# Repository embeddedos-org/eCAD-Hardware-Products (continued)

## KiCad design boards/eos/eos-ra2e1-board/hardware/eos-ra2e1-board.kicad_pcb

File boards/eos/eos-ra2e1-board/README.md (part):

# EoS RA2E1 Board

A Renesas RA2E1 (R7FA2E1A92DFM, Cortex-M23, LQFP-64) development board that fits Arduino Uno R3 shields and Digilent Pmod modules, 68.58 × 53.34 mm, two layers.
Designed by Kartikeydheer Srivastava. All rights reserved: not open source, and not under this repository's MIT licence.
Anyone may view it, clone this repository and run its tests; anything more needs
Kartikeydheer Srivastava's written permission (kartikeydheer@gmail.com). EmbeddedOS (EoS) Research Foundation has a limited, revocable
permission. See [LICENSE.txt](LICENSE.txt) and [the licence summary](../README.md#licence).

A board for the same job as Renesas' EK-RA2E1; an original design, not a copy: no file of the vendor's was used.
No design file of the vendor's was used (no schematic, layout, CAD, Gerbers or BOM of Renesas' was opened);
the header positions come from Matthew Beckler's "Arduino Uno R3" dimension drawing v1.05, the Arduino UNO R3 product reference manual (A000066),
section 5.4, and Digilent's Pmod Interface Specification (revised 29 September 2020), section 4 and Figure 5.
The circuit comes from Renesas' RA2E1 data sheet, hardware manual and application notes, and the other
chip makers' data sheets.

| | |
|---|---|
|  |  |

The RA2E1 runs at 3.3 V from its 48 MHz on-chip oscillator. One USB-C port powers the board and
carries a CP2102N USB-UART bridge on SCI9, the RA2E1's serial-programming port, so the same port is
the console and, with the MD jumper fitted, the flash programmer. An Arm 10-pin SWD header takes
any SWD probe. The I/O runs at 3.3 V: IOREF is 3.3 V, and most RA2E1 pins take at most VCC + 0.3 V.

## What is on it

Sources: **DS** = Renesas RA2E1 Group Datasheet R01DS0386EJ0170 Rev.1.70; **UM** = RA2E1 Group
User's Manual: Hardware R01UH0852EJ0170 Rev.1.70; **QDG** = RA2 Quick Design Guide R01AN6060EU0104
Rev.1.04; **E2** = E2/E2 Lite Notes on Connection of RA Devices R20UT4686EJ0360 Rev.3.60; **CLK** =
Design Guide for Main Clock Circuits and Sub Clock Circuits R01AN7202EJ0102 Rev.1.02.

| Block | What it is, and where each value comes from |
|---|---|
| MCU | R7FA2E1A92DFM, 128 KB flash, 16 KB SRAM, −40 to 85 °C, LQFP-64 10 × 10 mm, 0.5 mm pitch (DS Table 1.12). KiCad's stock LQFP-64_10x10mm_P0.5mm footprint, checked against both package drawings the DS gives this part (Appendix 2, Figures A2.1 PLQP0064KB-C and A2.2 PLQP0064KL-A: body 10.0 mm, lead span 12.0 mm, leads 0.15–0.27 mm wide, foot 0.45–0.75 mm). |
| Supplies | 0.1 µF at each VCC/VSS pair (11/8, 39/40) (DS 2.1); 4.7 µF ceramic on VCL, the internal regulator's output (UM Table 38.1). AVCC0 must equal VCC and rise with or after it (DS Table 2.2): it comes from 3.3 V through a Bourns MH1608-221Y bead, with 0.1 µF at the pin and 10 µF + 10 nF at the supply (UM Figure 29.33, reference values). VREFH0 is tied to AVCC0 and VREFL0 to AVSS0, with 0.1 µF between them (DS 2.1, Table 1.14; UM Table 17.4). |
| 3.3 V LDO | TI TPS7A91 (SBVS282A), 1 A, from the 5 V rail: R1 = 3.57 kΩ, R2 = 1.15 kΩ (3.283 V, Table 7-1, Panasonic ERA-2AEB 0.1 %), 10 µF in (16 V 0805, so the 5 V bias costs less of it than the 50 % that section 7.1.3 allows for) and out, EN tied to IN. The RA2E1 needs its supply to rise at 0.02–2 ms/V (DS Table 2.14; 2 ms/V the limit in SCI boot mode). The TPS7A91's ramp has limits: tSS = 0.8 V × CNR/SS / INR/SS (Equation 6), INR/SS = 4.0–9.0 µA (section 5.5), so 10 nF ±10 % gives 0.80–2.2 ms, 0.24–0.67 ms/V. A plain LDO gives only a typical start-up time. That sum assumes the 5 V rail itself rises faster than about 0.5 V/ms: with EN tied to IN, a slower 5 V (a bench supply on the shield's 5V pin) is followed by the output and can break the 2 ms/V limit. Firmware that sets OFS1.LVDAS = 0 (voltage monitor 0 reset on at start-up) removes the upper limit outside SCI boot mode (Table 2.14, note 1); SCI boot is entered with JP1 and the reset button, not by a power-on ramp. |
| Power input | USB-C as a 5 V sink (5.1 kΩ Rd on CC1, CC2; TI SLVSFJ9 section 10.3.14.2), Littelfuse 1206L050YR polyfuse (0.50 A hold, 1.00 A trip), then a Nexperia PMEG6010CEH Schottky to the 5 V rail, so 5 V fed into the shield 5V pin cannot reach the host. The shield's 3V3 and IOREF pins are outputs: fed with 3.3 V while the 5 V rail is off, they would lift the TPS7A91's OUT above IN + 0.3 V, its absolute maximum (SBVS282A 5.1). |
| Current and heat | Budget: 300 mA from USB in all, the board's own load included (the CP2102N about 13.7 mA transmitting at 3 Mbaud, typical, CP2102N Table 3.2; the four LEDs 8.4 mA). D1 then drops at most about 0.48 V (Table 7, between the 100 mA and 500 mA maxima), 0.14 W, which at 330 K/W (standard footprint, Nexperia's thermal table) is 48 °C over ambient. The TPS7A91 then sees at most about 4.9 V in (5.25 V less D1's drop) and dissipates (4.9 − 3.283) V × 0.3 A = 0.49 W. TI's 62.5 °C/W θJA is its JEDEC board with plated vias in the thermal pad (SBVS282A 5.4, 7.1.4); this 1.2 × 2.0 mm pad has none (the generator adds exposed-pad vias only above 2 mm), so this board's θJA is higher and unknown. With ψJB = 30.7 °C/W (7.1.5) the junction runs 15 °C above the board next to the package at that load, so the board there must stay under 110 °C for the 125 °C limit (5.3). Not measured. |
| USB ESD | Littelfuse SP0503BAHTG on D+, D− and VBUS: diodes to ground only, no path from D+ to VBUS (CP2102N data sheet Figure 2.5; Littelfuse SP05xxBA pinout, page 1: pin 1 common, pins 2–4 one diode each). |
| USB-UART | Silicon Labs CP2102N-A02-GQFN24 (data sheet Rev. 1.5) on SCI9, P109 TXD9 and P110 RXD9: UM Table 35.18 makes these SCI boot mode's only pins. It runs from the board's 3.3 V (Figure 2.3: VREGIN tied to VDD, VIO to VDD), so it is never unpowered while the RA2E1 is. 4.7 µF + 0.1 µF at VREGIN/VDD and at VIO, 1 kΩ RSTb pull-up (section 2.1). VBUS sense through 22.1 kΩ / 47.5 kΩ (Figure 2.5) plus a 1.5 kΩ bleed, so its D+ pull-up comes on only with a host present: with the board fed from the 5V pin, the Schottky's reverse leakage would need 599 µA to lift the VBUS pin above VIL = 0.6 V (Table 3.7). PMEG6010CEH Table 7 gives 0.8 µA typical at 5 V and 25 °C, and its Fig. 2 about 100 µA typical at 85 °C; no maximum is given at 5 V, and at 60 V and 25 °C the maximum is 4.5 times the typical, which at 85 °C would still be about 450 µA. The bleed costs 3.4 mA from a host. |
| Clocks | No main crystal: the HOCO stays within ±1 % at 48 MHz over −40 to 105 °C and 1.6–5.5 V (DS Table 2.21, QDG 5.6), enough for the SCIs, SPI and IIC; the RA2E1 has no USB. EXTAL and XTAL serve as SCI1 for D0/D1 (UM Table 17.4). Sub-clock fitted, since the RTC counts the sub-clock or the LOCO (UM 22.1) and the LOCO is ±15 % (DS Table 2.21): Abracon ABS07-32.768KHZ-9-T (CL 9 pF, ESR ≤ 70 kΩ), 15 pF on XCIN and 18 pF on XCOUT, no damping resistor, Standard CL drive (SOMCR.SODRV = 00): CLK Table 4.2.7, the Renesas matching result for the RA2E1's group, which allows up to 120 kΩ ESR. Layout (CLK 6.1.1, 6.1.4): pin → crystal pad → load capacitor laid first on the top layer with no via, XCOUT 4.9 mm and XCIN 5.8 mm to the crystal, 0.35 mm apart, with VSS pin 8's track to C1 between D1 and XCOUT. D0 and D1 drop through vias just inside the chip outline and leave north-east on the bottom layer; TXD9 and RXD9 run south of the LEDs. None of the pre-laid copper of another net is in the crystal area on either layer; see the last section for the autorouter's nets. |
| Reset, mode, NMI | RES: 10 kΩ pull-up (E2 Figure 2.7: 4.7–10 kΩ), no capacitor (QDG 6.2), a reset button; RES also goes to the SWD header and the Uno RESET pin. MD: internal pull-up on during reset (UM Table A1.1), and JP1 (a 2-pin header with a shunt) with 1.5 kΩ to ground (E2 Figure 2.9): fitted at reset is SCI boot mode (UM Table 3.1). With it fitted MD is at most 0.43 V, under VIL = 0.66 V (DS Tables 2.5 and 2.10). P200/NMI: 10 kΩ pull-up (UM Table 17.4). |
| Debug | Arm Cortex 10-pin 1.27 mm SWD header in place of the vendor kit's J-Link OB probe, whose firmware is SEGGER's: SWDIO P108, SWCLK P300, nRESET, VTref 3.3 V (QDG Figure 1). Both SWD pins have internal pull-ups on by default (QDG 2), so none are fitted. The RA2E1 has no SWO (DS Table 1.14), so pins 6 and 8 are open. Renesas' E2 and E2 Lite use those two pins for TxD9 and RxD9, flash programming through the emulator (R20UT4686 Table 2.3); they stay open here because the CP2102N already drives RXD9, so program through the CP2102N (SCI boot) or over SWD. |
| Pmod ports | Two 2×6 right-angle female host ports on the left edge, 0.9 in apart, the 7–12 row 10.16 mm and the 1–6 row 12.70 mm from the edge, pin 1 as in the specification's Figure 5; 3.3 V only (its reduced subset). J7, Type 2A (expanded SPI) on the RA2E1's SPI; J8, Type 6A (expanded I²C) on IIC0. Pin map below. |
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
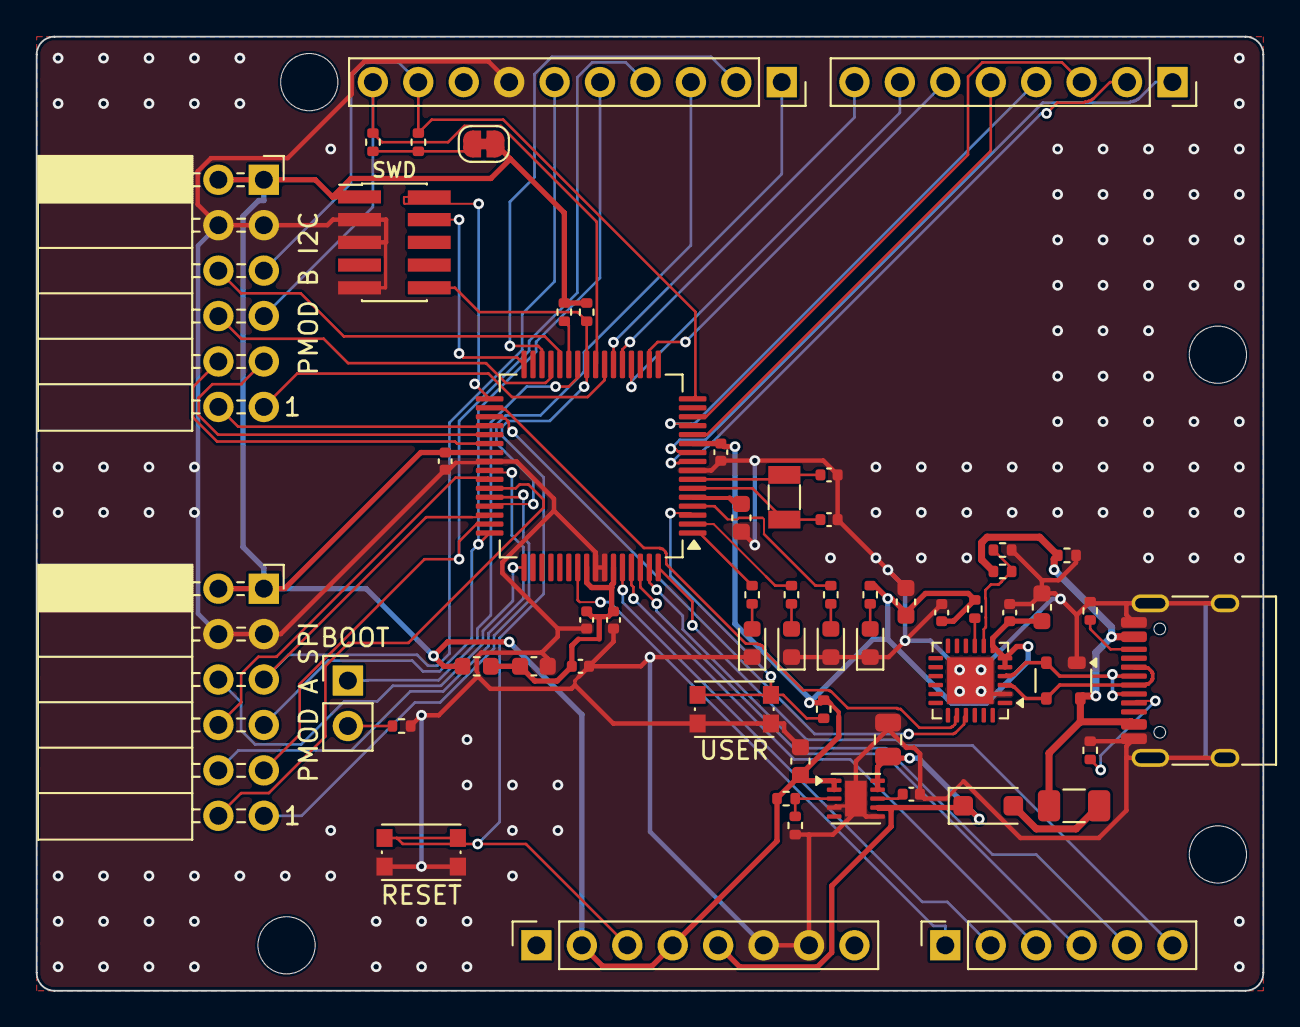
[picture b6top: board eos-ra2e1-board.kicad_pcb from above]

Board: 2 copper layers, 68.6 x 53.3 mm, 62 parts (1 on the bottom side), 67 nets.

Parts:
C1, C2, C6, C7, C17, C19: 100n; C_0402_1005Metric
C3, C16, C18: 4.7u; C_0603_1608Metric
C4: 18p; C_0402_1005Metric
C5: 15p; C_0402_1005Metric
C8, C14: 10u; C_0603_1608Metric
C9, C15: 10n; C_0402_1005Metric
C13: 10u; C_0805_2012Metric
D1: PMEG6010CEH; D_SOD-123F
D2: PWR; LED_0603_1608Metric
D3: LED1; LED_0603_1608Metric
D4: LED2; LED_0603_1608Metric
D5: LED3; LED_0603_1608Metric
F1: 500mA; Fuse_1206_3216Metric
FB1: 220R; L_0603_1608Metric
H1, H2, H3, H4: M3; MountingHole_3.2mm_M3_ISO14580
J1: USB-C; USB_C_Receptacle_HRO_TYPE-C-31-M-12
J2: SWD; PinHeader_2x05_P1.27mm_Vertical_SMD
J3: D8-SCL; PinSocket_1x10_P2.54mm_Vertical
J4: D0-D7; PinSocket_1x08_P2.54mm_Vertical
J5: POWER; PinSocket_1x08_P2.54mm_Vertical
J6: A0-A5; PinSocket_1x06_P2.54mm_Vertical
J7: PMOD A; PinSocket_2x06_P2.54mm_Horizontal
J8: PMOD B; PinSocket_2x06_P2.54mm_Horizontal
JP1: MD; PinHeader_1x02_P2.54mm_Vertical
JP2: I2C PU; SolderJumper-2_P1.3mm_Bridged_RoundedPad1.0x1.5mm
R1, R2: 5.1k; R_0402_1005Metric
R3, R4: 2.2k; R_0402_1005Metric
R5: 22.1k; R_0402_1005Metric
R6: 47.5k; R_0402_1005Metric
R7, R14: 1.5k; R_0402_1005Metric
R8: 3.57k; R_0402_1005Metric
R9: 1.15k; R_0402_1005Metric
R10, R17, R18: 680; R_0402_1005Metric
R11: 1k; R_0402_1005Metric
R12, R13, R15: 10k; R_0402_1005Metric
R16: 750; R_0402_1005Metric
SW1: RESET; SW_Push_1P1T_NO_CK_KMR2
SW2: USER; SW_Push_1P1T_NO_CK_KMR2
U1: R7FA2E1A92DFM; LQFP-64_10x10mm_P0.5mm
U2: SP0503BAHTG; SOT-143
U3: CP2102N-A02-GQFN24; QFN-24-1EP_4x4mm_P0.5mm_EP2.6x2.6mm
U4: TPS7A91; Texas_S-PDSO-N10_EP1.2x2mm
Y1: 32.768kHz; Crystal_SMD_3215-2Pin_3.2x1.5mm

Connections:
+3V3: C1.1, C2.1, C14.1, C16.1, C17.1, C18.1, C19.1, FB1.1, J2.1, J5.2, J5.4, J7.1, J7.2, J8.1, J8.2, JP2.2, R8.1, R10.2, R11.2, R12.2, R13.2, R15.2, U1.11, U1.39, U3.5, U3.6, U3.7, U4.1, U4.2
+5V: C13.1, D1.1, J5.5, U4.7, U4.9, U4.10
/A0: J6.1, U1.55
/A1: J6.2, U1.60
/A2: J6.3, U1.61
/A3: J6.4, U1.62
/A4: J6.5, U1.63
/A5: J6.6, U1.64
/AVCC0: C6.1, C7.1, C8.1, C9.1, FB1.2, U1.56, U1.59
/CC1: J1.A5, R1.1
/CC2: J1.B5, R2.1
/CP_RST: R11.1, U3.9
/CP_VBUS: R5.2, R6.1, U3.8
/D0: J4.1, U1.10
/D1: J4.2, U1.9
/D2: J4.3, U1.14
/D3: J4.4, U1.13
/D4: J4.5, U1.12
/D5: J4.6, U1.18
/D6: J4.7, U1.20
/D7: J4.8, U1.21
/D8: J3.1, U1.22
/D9: J3.2, U1.30
/D10: J3.3, U1.45
/I2C_PU: JP2.1, R3.1, R4.1
/LDO_FB: R8.2, R9.1, U4.3
/LDO_NR: C15.1, U4.8
/LED1: R16.2, U1.1
/LED1_A: D3.2, R16.1
/LED2: R17.2, U1.2
/LED2_A: D4.2, R17.1
/LED3: R18.2, U1.4
/LED3_A: D5.2, R18.1
/LED_PWR_A: D2.2, R10.1
/MD: JP1.1, U1.26
/MD_JP: JP1.2, R14.1
/NMI: R13.1, U1.27
/PMODA_CS: J7.11, U1.44
/PMODA_CS2: J7.8, U1.42
/PMODA_CS3: J7.6, U1.49
/PMODA_INT: J7.12, U1.43
/PMODA_RST: J7.10, U1.41
/PMODB_INT: J8.11, U1.23
/PMODB_IO7: J8.12, U1.36
/PMODB_IO8: J8.10, U1.38
/PMODB_IO9: J8.8, U1.29
/PMODB_IO10: J8.6, U1.28
/PMODB_RST: J8.9, U1.37
/RES: J2.10, J5.3, R12.1, SW1.1, U1.25
/RXD9: U1.35, U3.21
/SCL: J3.10, J8.7, R3.2, U1.24
/SDA: J3.9, J8.5, R4.2, U1.16
/SPI_MISO: J3.5, J7.7, U1.48
/SPI_MOSI: J3.4, J7.9, U1.47
/SPI_SCK: J3.6, J7.5, U1.46
/SWCLK: J2.4, U1.32
/SWDIO: J2.2, U1.33
/TXD9: U1.34, U3.20
/USB_DM: J1.A7, J1.B7, U2.2, U3.4
/USB_DP: J1.A6, J1.B6, U2.3, U3.3
/USER_BTN: R15.1, SW2.1, U1.3
/VBUS: F1.1, J1.A4, J1.A9, J1.B4, J1.B9, R5.1, R7.1, U2.4
/VBUS_F: D1.2, F1.2
/VCL: C3.1, U1.5
/XCIN: C5.1, U1.6, Y1.2
/XCOUT: C4.1, U1.7, Y1.1
GND: C1.2, C2.2, C3.2, C4.2, C5.2, C6.2, C7.2, C8.2, C9.2, C13.2, C14.2, C15.2, C16.2, C17.2, C18.2, C19.2, D2.1, D3.1, D4.1, D5.1, J1.A1, J1.A12, J1.B1, J1.B12, J1.SH, J2.3, J2.5, J2.9, J3.7, J5.6, J5.7, J7.3, J7.4, J8.3, J8.4, R1.2, R2.2, R6.2, R7.2, R9.2, R14.2, SW1.2, SW2.2, U1.8, U1.40, U1.57, U1.58, U2.1, U3.2, U3.25, U4.4, U4.6, U4.11

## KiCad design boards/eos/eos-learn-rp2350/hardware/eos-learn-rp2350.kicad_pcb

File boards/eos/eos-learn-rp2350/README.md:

# EoS Learn RP2350

A four-layer RP2350A teaching board, 52.6 × 51.6 mm. Designed by Kartikeydheer Srivastava.
All rights reserved: not open source, and not under this repository's MIT licence.
Anyone may view it, clone this repository and run its tests; anything more needs
Kartikeydheer Srivastava's written permission (kartikeydheer@gmail.com). EmbeddedOS (EoS) Research Foundation has a limited, revocable
permission. See [LICENSE.txt](LICENSE.txt) and [the licence summary](../README.md#licence).

| | |
|---|---|
|  |  |

## What is on it

- **RP2350A**, 12 MHz crystal (ABM8-272-T3, 15 pF load capacitors, 1 kΩ series resistor) and
  128 Mbit QSPI flash (W25Q128JV).
- **Core regulator** (the RP2350's internal switcher): 3.3 µH polarity-marked AOTA-B201610S3R3-101-T
  inductor, 4.7 µF on VREG_VIN and on the output, 33 Ω + 4.7 µF filter on VREG_AVDD.
- **USB-C** (5 V sink, 5.1 kΩ on CC1 and CC2), USBLC6-2SC6 ESD protection and 27 Ω series
  resistors at the chip.
- **Power path:** a 500 mA polyfuse, then a Schottky diode, so 5 V fed into the header can
  power the board but never reach the USB host. Then an AP7361C 3.3 V regulator, which Diodes
  Inc. rates stable with ceramic capacitors of 2.2 µF or more, like those on this board.
- **BOOTSEL and RUN** buttons, a power LED and a user LED on GPIO25.
- **All 30 GPIOs** on two 1×20, 2.54 mm headers, in pin order, with ground pins spread along both.
- **Qwiic** (I2C0 on GPIO4/5, 4.7 kΩ pull-ups) and a Raspberry Pi Debug Probe **SWD** connector.

Every value comes from Raspberry Pi's *Hardware design with RP2350* and the RP2350 datasheet.

## The core layout is Raspberry Pi's, exactly

The RP2350 datasheet says the regulator's inductor "must be ... placed on the layout as indicated
in Figure 26". Raspberry Pi publishes that layout, the RP2350A Minimal Design R4, under the MIT
licence. So everything around the chip is theirs, unchanged:

- the footprints and positions of the chip, its regulator, the decoupling (all but C17, this
  board's own capacitor on ADC_AVDD), the crystal circuit, the USB resistors and the flash;
- the copper between them: 124 tracks, 25 vias and 7 zones.

`tests/unit/test_eos_boards.py` checks where those parts sit, and the copper between them, down
to KiCad's 1 nm resolution, every time the test suite runs. It compares the board with the
reference file. The reference file records the SHA-256 of the Raspberry Pi design it was taken
from, and a test re-extracts it from that design when you supply the file (`RPI_MINIMAL_PCB`). The GPIO lines leave the chip along
Raspberry Pi's own escape paths; from there to the headers, the routing is this board's.

Raspberry Pi's licence requires its notice to travel with the design. It is on the back
silkscreen and in [hardware/footprints/EoS_RPi_Reference.LICENSE.txt](hardware/footprints/EoS_RPi_Reference.LICENSE.txt).

## Build results

| Check | Result |
|---|---|
| Schematic ERC | 0 violations |
| DRC errors | 0 |
| Unconnected items | 0 |
| Schematic ↔ board parity | 0 differences |
| DRC warnings | 4, explained below |

The four warnings:

- **Two short 3.3 V track ends.** These are Raspberry Pi's copper, kept unchanged. On their
  two-layer board those tracks ran into a 3.3 V pour; this four-layer board feeds 3.3 V from an
  inner plane instead.
- **Two USB-C silkscreen lines clipped at the board edge.** The connector is meant to sit on the
  edge.

## Fabrication

4 layers (signal / GND plane / 3.3 V plane / signal), 1.6 mm thick. Measured from the board file:

- **Tracks:** 0.15 mm, narrowing to 0.112 mm where the router necks down at a 0.4 mm-pitch pin.
- **Clearance:** 0.15 mm, and 0.125 mm at Raspberry Pi's regulator capacitor pads, as their
  footprints specify (the board's floor is 0.1 mm so that applies).
- **Vias:** 0.6 mm with a 0.3 mm drill; Raspberry Pi's own copper uses a 0.25 mm drill.
- **Holes:** at least 0.25 mm apart.

- Gerbers and drill files: [fab/gerbers](fab/gerbers)
- Bill of materials: [fab/eos-learn-rp2350-bom.csv](fab/eos-learn-rp2350-bom.csv)
- Pick-and-place: [fab/eos-learn-rp2350-placement.csv](fab/eos-learn-rp2350-placement.csv)
- STEP model: [fab/eos-learn-rp2350.step](fab/eos-learn-rp2350.step)
- Schematic: [eos-learn-rp2350-schematic.pdf](eos-learn-rp2350-schematic.pdf)
- KiCad project: [hardware](hardware)

## What has not been done

- **No board has been made or powered.** These are design files that pass KiCad's electrical and
  design rule checks; no hardware has been tested.
- **No signal-integrity simulation.** USB and QSPI were not simulated; the QSPI routing is
  Raspberry Pi's own.

## Rebuild

```
python3 tools/eos_boards/build.py eos_learn_rp2350
```

The design file is [tools/eos_boards/boards/eos_learn_rp2350.py](../../../tools/eos_boards/boards/eos_learn_rp2350.py).

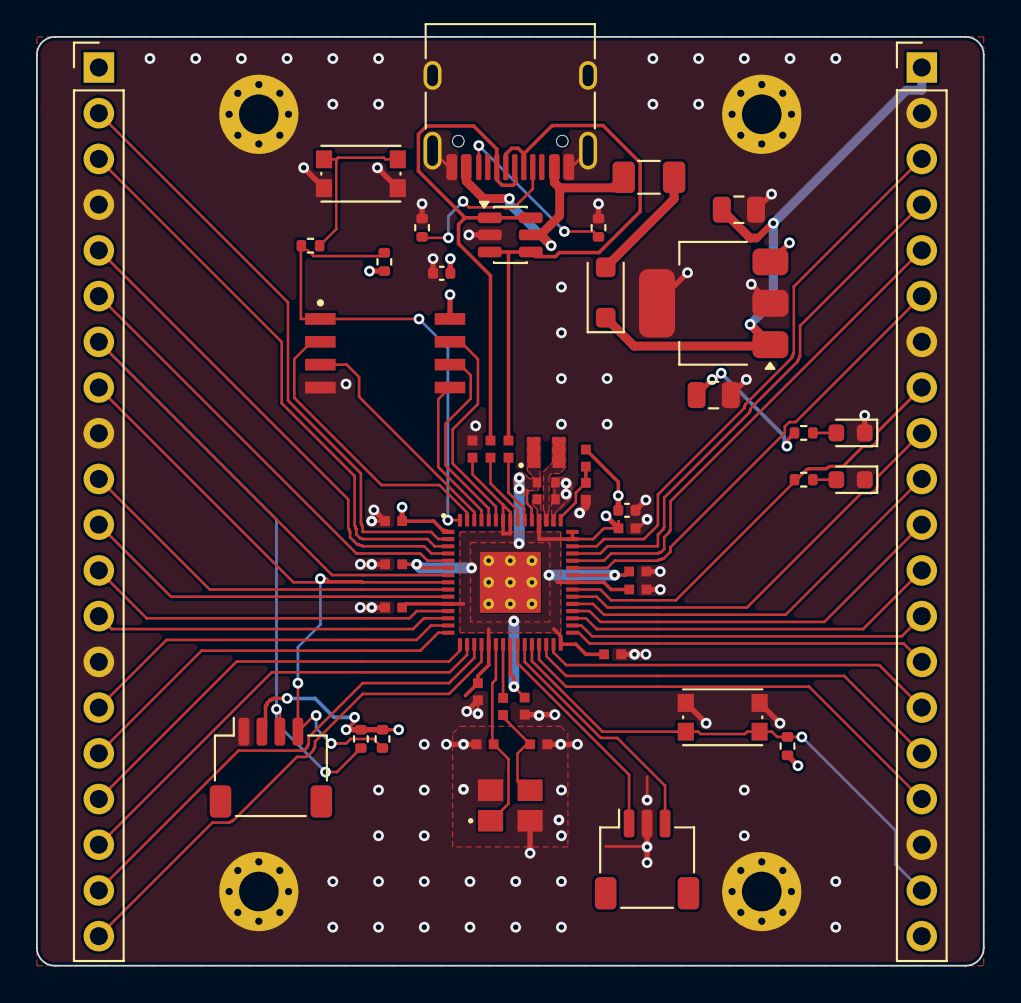
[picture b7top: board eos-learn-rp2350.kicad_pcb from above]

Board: 4 copper layers, 52.6 x 51.6 mm, 53 parts (0 on the bottom side), 59 nets.

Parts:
C1, C2: 10u; C_0805_2012Metric
C3, C4: 15p; generic_capc1005x50
C6, C7: 4.7u; generic_capc1005x50_wide
C9: 4.7u; generic_capc1005x50
C10, C11, C12, C13, C14, C15, C16, C18, C19, C20: 100n; generic_capc1005x50
C17, C21: 100n; C_0402_1005Metric
D1: MBR120VLSFT1G; D_SOD-123F
D2: PWR; LED_0603_1608Metric
D3: GP25; LED_0603_1608Metric
F1: 500mA; Fuse_1206_3216Metric
H1, H2, H3, H4: M2; MountingHole_2.2mm_M2_Pad_Via
J1: USB-C; USB_C_Receptacle_HRO_TYPE-C-31-M-12
J2: GPIO 0-15; PinHeader_1x20_P2.54mm_Vertical
J3: Power, GPIO 16-29; PinHeader_1x20_P2.54mm_Vertical
J4: SWD; JST_SH_SM03B-SRSS-TB_1x03-1MP_P1.00mm_Horizontal
J5: Qwiic; JST_SH_SM04B-SRSS-TB_1x04-1MP_P1.00mm_Horizontal
L1: 3.3u; abracon_aota-b201610s3r3-101-t
R1, R2: 5.1k; R_0402_1005Metric
R3, R4: 27; generic_resc1005x35
R5, R8: 1k; R_0402_1005Metric
R6: 33; generic_resc1005x35
R7, R9: 10k; R_0402_1005Metric
R10: 1k; generic_resc1005x35
R11: 470; R_0402_1005Metric
R12, R13: 4.7k; R_0402_1005Metric
SW1: BOOTSEL; SW_Push_1P1T_NO_CK_KMR2
SW2: RUN; SW_Push_1P1T_NO_CK_KMR2
U1: RP2350A; rpi_rp2350a_vias
U2: USBLC6-2SC6; SOT-23-6
U3: AP7361C-33; SOT-223-3_TabPin2
U4: W25Q128JVS; generic_soic127p790x195-8
Y1: 12MHz; generic_xtalcc320x250x80-4

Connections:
+1V1: C7.1, C18.1, C19.1, C20.1, L1.1, U1.6 (DVDD), U1.23 (DVDD), U1.39 (DVDD), U1.50 (VREG_FB)
+3V3: C2.1, C6.1, C10.1, C11.1, C12.1, C13.1, C14.1, C15.1, C16.1, C17.1, C21.1, J2.1, J3.20, J5.2, R5.1, R6.1, R7.2, R9.2, R12.2, R13.2, U1.1 (IOVDD), U1.11 (IOVDD), U1.20 (IOVDD), U1.30 (IOVDD), U1.38 (IOVDD), U1.44 (ADC_AVDD), U1.45 (IOVDD), U1.49 (VREG_VIN), U1.53 (USB_OTP_VDD), U1.54 (QSPI_IOVDD), U3.3, U4.8 (VCC)
+5V: C1.1, D1.1, J3.1, U3.1
/BOOTSEL: R8.2, SW1.1
/CC1: J1.A5, R1.1
/CC2: J1.B5, R2.1
/GPIO0: J2.2, U1.2 (GPIO0)
/GPIO1: J2.3, U1.3 (GPIO1)
/GPIO2: J2.5, U1.4 (GPIO2)
/GPIO3: J2.6, U1.5 (GPIO3)
/GPIO4: J2.7, J5.3, R12.1, U1.7 (GPIO4)
/GPIO5: J2.8, J5.4, R13.1, U1.8 (GPIO5)
/GPIO6: J2.10, U1.9 (GPIO6)
/GPIO7: J2.11, U1.10 (GPIO7)
/GPIO8: J2.12, U1.12 (GPIO8)
/GPIO9: J2.13, U1.13 (GPIO9)
/GPIO10: J2.15, U1.14 (GPIO10)
/GPIO11: J2.16, U1.15 (GPIO11)
/GPIO12: J2.17, U1.16 (GPIO12)
/GPIO13: J2.18, U1.17 (GPIO13)
/GPIO14: J2.19, U1.18 (GPIO14)
/GPIO15: J2.20, U1.19 (GPIO15)
/GPIO16: J3.17, U1.27 (GPIO16)
/GPIO17: J3.16, U1.28 (GPIO17)
/GPIO18: J3.15, U1.29 (GPIO18)
/GPIO19: J3.14, U1.31 (GPIO19)
/GPIO20: J3.13, U1.32 (GPIO20)
/GPIO21: J3.12, U1.33 (GPIO21)
/GPIO22: J3.11, U1.34 (GPIO22)
/GPIO23: J3.10, U1.35 (GPIO23)
/GPIO24: J3.9, U1.36 (GPIO24)
/GPIO25: J3.8, R11.1, U1.37 (GPIO25)
/GPIO26_ADC0: J3.6, U1.40 (GPIO26_ADC0)
/GPIO27_ADC1: J3.5, U1.41 (GPIO27_ADC1)
/GPIO28_ADC2: J3.4, U1.42 (GPIO28_ADC2)
/GPIO29_ADC3: J3.3, U1.43 (GPIO29_ADC3)
/LED_PWR_A: D2.2, R5.2
/LED_USR_A: D3.2, R11.2
/QSPI_SCLK: U1.56 (QSPI_SCLK), U4.6 (CLK)
/QSPI_SD0: U1.57 (QSPI_SD0), U4.5 (DI_IO0)
/QSPI_SD1: U1.59 (QSPI_SD1), U4.2 (DO_IO1)
/QSPI_SD2: U1.58 (QSPI_SD2), U4.3 (~WP_IO2)
/QSPI_SD3: U1.55 (QSPI_SD3), U4.7 (~HOLD_IO3)
/QSPI_SS: R7.1, R8.1, U1.60 (QSPI_~SS), U4.1 (~CS)
/RP_USB_DM: R4.2, U1.51 (USB_DM)
/RP_USB_DP: R3.2, U1.52 (USB_DP)
/RUN: J3.19, R9.1, SW2.1, U1.26 (RUN)
/SWCLK: J4.1, U1.24 (SWCLK)
/SWDIO: J4.3, U1.25 (SWDIO)
/USB_D+: J1.A6, J1.B6, R3.1, U2.1, U2.6
/USB_D-: J1.A7, J1.B7, R4.1, U2.3, U2.4
/VBUS_F: D1.2, F1.2
/VREG_AVDD: C9.1, R6.2, U1.46 (VREG_AVDD)
/VREG_LX: L1.2, U1.48 (VREG_LX)
/XIN: C3.1, U1.21 (XIN), Y1.1
/XOUT: R10.1, U1.22 (XOUT)
/XTAL_OUT: C4.1, R10.2, Y1.3
GND: C1.2, C2.2, C3.2, C4.2, C6.2, C7.2, C9.2, C10.2, C11.2, C12.2, C13.2, C14.2, C15.2, C16.2, C17.2, C18.2, C19.2, C20.2, C21.2, D2.1, D3.1, H1.1, H2.1, H3.1, H4.1, J1.A1, J1.A12, J1.B1, J1.B12, J1.SH, J2.4, J2.9, J2.14, J3.2, J3.7, J3.18, J4.2, J5.1, R1.2, R2.2, SW1.2, SW2.2, U1.47 (VREG_PGND), U1.61 (GND), U2.2, U3.2, U4.4 (GND), Y1.2, Y1.4
VBUS: F1.1, J1.A4, J1.A9, J1.B4, J1.B9, U2.5

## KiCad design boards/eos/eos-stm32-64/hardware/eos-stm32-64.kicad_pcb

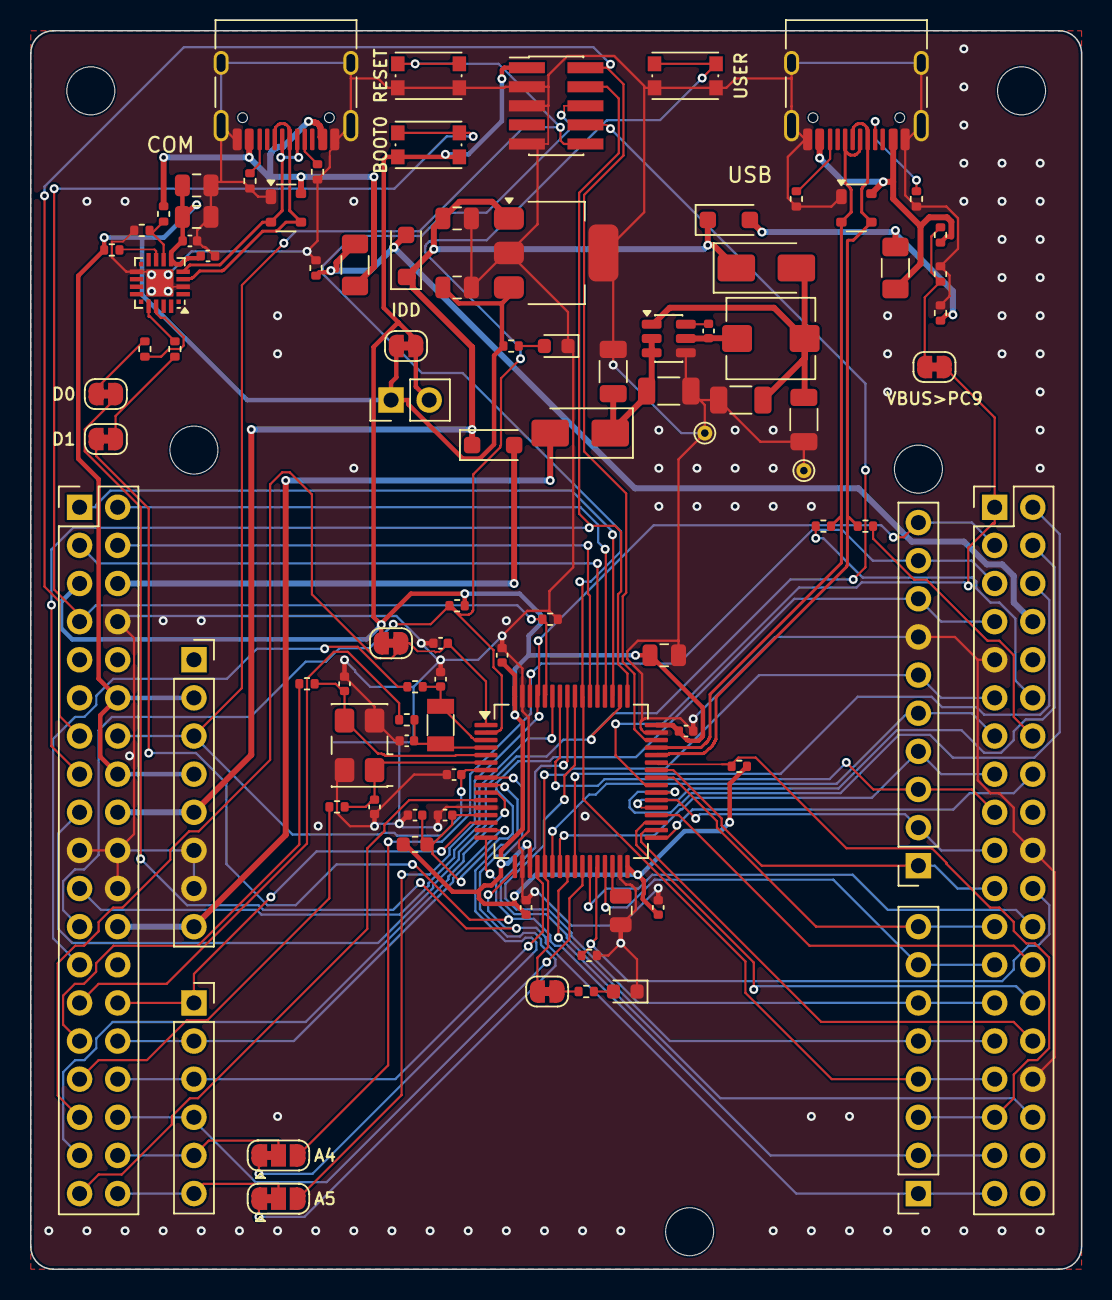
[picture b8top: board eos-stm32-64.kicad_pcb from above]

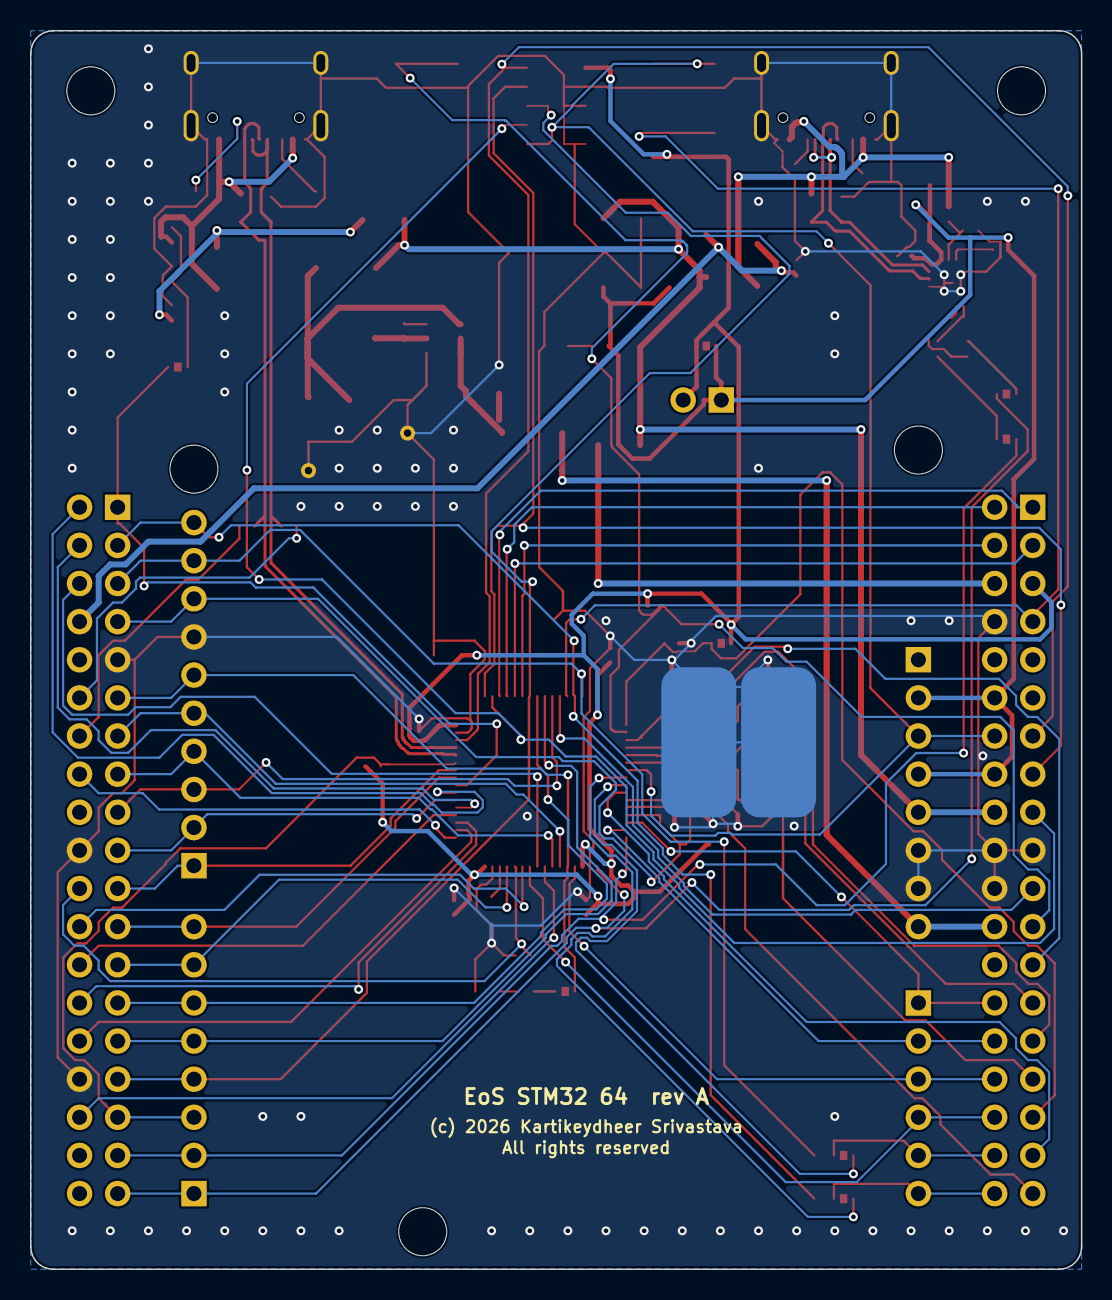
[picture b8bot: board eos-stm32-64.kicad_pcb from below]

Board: 2 copper layers, 70.0 x 82.5 mm, 99 parts (3 on the bottom side), 93 nets.

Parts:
B1: USER; SW_Push_1P1T_NO_CK_KMR2
B2: RESET; SW_Push_1P1T_NO_CK_KMR2
B3: BOOT0; SW_Push_1P1T_NO_CK_KMR2
C1, C3, C9, C10, C15, C16: 4.7u; C_0805_2012Metric
C2, C4, C6, C11, C12, C13, C14, C18, C19, C20: 100n; C_0402_1005Metric
C5, C25: 10u; C_1206_3216Metric
C7, C8: 22u; C_1206_3216Metric
C17: 1u; C_0402_1005Metric
C21, C22: 12p; C_0402_1005Metric
C23, C24: 3.9p; C_0402_1005Metric
CN5: D8-D15; PinSocket_1x10_P2.54mm_Vertical
CN6: POWER; PinSocket_1x08_P2.54mm_Vertical
CN7: CN7; PinHeader_2x19_P2.54mm_Vertical
CN8: ANALOG; PinSocket_1x06_P2.54mm_Vertical
CN9: D0-D7; PinSocket_1x08_P2.54mm_Vertical
CN10: CN10; PinHeader_2x19_P2.54mm_Vertical
D1, D2, D3: PMEG3010CEH; D_SOD-123F
D4, D5: B240A; D_SMA
F1, F2: 500mA; Fuse_1206_3216Metric
FB1: 600R; L_0603_1608Metric
H1, H2, H3, H4, H5: M3; MountingHole_3.2mm_M3_ISO14580
J1, J2: USB-C; USB_C_Receptacle_HRO_TYPE-C-31-M-12
J3: Cortex Debug; PinHeader_2x05_P1.27mm_Vertical_SMD
J4: IDD; PinHeader_1x02_P2.54mm_Vertical
JP1: IDD; SolderJumper-2_P1.3mm_Bridged_RoundedPad1.0x1.5mm
JP2: VBAT; SolderJumper-2_P1.3mm_Bridged_RoundedPad1.0x1.5mm
JP3: LD2; SolderJumper-2_P1.3mm_Bridged_RoundedPad1.0x1.5mm
JP4: A4; SolderJumper-3_P1.3mm_Bridged12_RoundedPad1.0x1.5mm
JP6: A5; SolderJumper-3_P1.3mm_Bridged12_RoundedPad1.0x1.5mm
JP7: VBUS>PC9; SolderJumper-2_P1.3mm_Bridged_RoundedPad1.0x1.5mm
JP8: D0; SolderJumper-2_P1.3mm_Bridged_RoundedPad1.0x1.5mm
JP9: D1; SolderJumper-2_P1.3mm_Bridged_RoundedPad1.0x1.5mm
L1: 4.7u; L_Bourns_SRP5030T
LD2: USER; LED_0603_1608Metric
LD3: PWR; LED_0603_1608Metric
R1, R2, R9, R10: 5.1k; R_0402_1005Metric
R3, R23: 4.7k; R_0402_1005Metric
R4, R7, R8: 1k; R_0402_1005Metric
R5, R11: 22.1k; R_0402_1005Metric
R6, R12: 47.5k; R_0402_1005Metric
R13: 750; R_0402_1005Metric
R14, R15, R16: 10k; R_0402_1005Metric
R17: 680; R_0402_1005Metric
R18, R19, R20, R21, R24, R25: 0; R_0402_1005Metric
R22: 47k; R_0402_1005Metric
TP1, TP2: GND; SolderWirePad_1x01_SMD_5x10mm
TP3, TP4: GND; TestPoint_THTPad_D1.0mm_Drill0.5mm
U1: STM32F411RET6; LQFP-64_10x10mm_P0.5mm
U2: CP2102N-A02-GQFN20; SiliconLabs_QFN-20-1EP_3x3mm_P0.5mm_EP1.8x1.8mm
U3: AP7361C-33; SOT-223-3_TabPin2
U4: AP63205; TSOT-23-6
U5, U6: SP0503BAHTG; SOT-143
Y1: 8MHz; Crystal_SMD_5032-4Pin_5.0x3.2mm
Y2: 32.768kHz; Crystal_SMD_3215-2Pin_3.2x1.5mm

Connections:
+3V3: C1.1, C2.1, C3.1, C4.1, C10.1, CN6.2, CN6.4, CN7.12, CN7.16, J4.1, JP1.1, R4.2, R13.1, U2.6, U2.7, U3.3
+5V: C9.1, CN6.5, CN7.18, D1.1, D2.1, D3.1, D5.1, U3.1
/5V_BUCK: C7.2, C8.2, D5.2, L1.2, U4.1
/A4: CN7.36, CN8.5, JP4.2
/A5: CN7.38, CN8.6, JP6.2
/BOOT0: B3.1, CN7.7, R14.1, U1.60
/BUCK_BST: C6.2, U4.6
/BUCK_SW: C6.1, L1.1, U4.5
/CC1_USB: J2.A5, R9.1
/CC1_VCP: J1.A5, R1.1
/CC2_USB: J2.B5, R10.1
/CC2_VCP: J1.B5, R2.1
/E5V: CN7.6, D3.2
/LD2_A: LD2.2, R17.2
/LD2_J: JP3.2, R17.1
/LED_PWR_A: LD3.2, R13.2
/NRST: B2.1, C20.1, CN6.3, CN7.14, J3.10, U1.7
/PA0: CN7.28, CN8.1, U1.14
/PA1: CN7.30, CN8.2, U1.15
/PA2: CN9.2, CN10.35, JP9.1, U1.16
/PA3: CN9.1, CN10.37, JP8.2, U1.17
/PA4: CN7.32, CN8.3, U1.20
/PA5: CN5.6, CN10.11, JP3.1, U1.21
/PA6: CN5.5, CN10.13, U1.22
/PA7: CN5.4, CN10.15, U1.23
/PA8: CN9.8, CN10.23, U1.41
/PA9: CN5.1, CN10.21, U1.42
/PA10: CN9.3, CN10.33, R22.1, U1.43
/PA11_HDR: CN10.14, R25.1
/PA12_HDR: CN10.12, R24.1
/PA13: CN7.13, J3.2, U1.46
/PA14: CN7.15, J3.4, U1.49
/PA15: CN7.17, J3.8, U1.50
/PB0: CN7.34, CN8.4, U1.26
/PB1: CN10.24, U1.27
/PB2: CN10.22, R15.1, U1.28
/PB3: CN9.4, CN10.31, J3.6, U1.55
/PB4: CN9.6, CN10.27, U1.56
/PB5: CN9.5, CN10.29, U1.57
/PB6: CN5.3, CN10.17, U1.58
/PB7: CN7.21, U1.59
/PB8: CN5.10, CN10.3, JP6.3, U1.61
/PB9: CN5.9, CN10.5, JP4.3, U1.62
/PB10: CN9.7, CN10.25, U1.29
/PB12: CN10.16, U1.33
/PB13: CN10.30, U1.34
/PB14: CN10.28, U1.35
/PB15: CN10.26, U1.36
/PC0: JP6.1, U1.8
/PC1: JP4.1, U1.9
/PC2: CN7.35, U1.10
/PC3: CN7.37, U1.11
/PC4: CN10.34, U1.24
/PC5: CN10.6, U1.25
/PC6: CN10.4, U1.37
/PC7: CN5.2, CN10.19, U1.38
/PC8: CN10.2, U1.39
/PC9: CN10.1, JP7.2, U1.40
/PC10: CN7.1, U1.51
/PC11: CN7.2, U1.52
/PC12: CN7.3, U1.53
/PC13: B1.1, CN7.23, R16.1, U1.2
/PC14: C23.1, R20.2, U1.3, Y2.1
/PC14_HDR: CN7.25, R20.1
/PC15: C24.2, R21.2, U1.4, Y2.2
/PC15_HDR: CN7.27, R21.1
/PD2: CN7.4, U1.54
/PH0: C21.1, R18.2, U1.5, Y1.3
/PH0_HDR: CN7.29, R18.1
/PH1: C22.2, R19.2, U1.6, Y1.1
/PH1_HDR: CN7.31, R19.1
/U5V: CN10.8, D1.2, F1.2, R3.1
/USB_DM: J2.A7, J2.B7, R25.2, U1.44, U6.3
/USB_DP: J2.A6, J2.B6, R24.2, U1.45, U6.2
/VBAT: C19.2, CN7.33, JP2.2, U1.1
/VBUS_USB: F2.1, J2.A4, J2.A9, J2.B4, J2.B9, R11.1, U6.4
/VBUS_VCP: F1.1, J1.A4, J1.A9, J1.B4, J1.B9, R5.1, U5.4
/VCAP1: C16.2, U1.30
/VCP_D+: J1.A6, J1.B6, U2.4, U5.3
/VCP_D-: J1.A7, J1.B7, U2.5, U5.2
/VCP_RST: R4.1, U2.9
/VCP_RXD: R8.2, U2.17
/VCP_RX_J: JP9.2, R8.1
/VCP_TXD: R7.1, U2.18
/VCP_TX_J: JP8.1, R7.2
/VCP_VBUS: R5.2, R6.1, U2.8
/VDDA: C17.2, C18.2, CN5.8, CN10.7, FB1.2, U1.13
/VDD_MCU: B3.2, C11.1, C12.1, C13.1, C14.1, C15.1, CN7.5, FB1.1, J3.1, J4.2, JP1.2, JP2.1, R16.2, R22.2, U1.19, U1.32, U1.48, U1.64
/VIN: CN6.8, CN7.24, D4.2
/VIN_P: C5.1, C25.1, D4.1, U4.2, U4.3
/VUSB: D2.2, F2.2, R23.1
/VUSB_SENSE: JP7.1, R11.2, R12.1
GND: B1.2, B2.2, C1.2, C2.2, C3.2, C4.2, C5.2, C7.1, C8.1, C9.2, C10.2, C11.2, C12.2, C13.2, C14.2, C15.2, C16.1, C17.1, C18.1, C19.1, C20.2, C21.2, C22.1, C23.2, C24.1, C25.2, CN5.7, CN6.6, CN6.7, CN7.8, CN7.19, CN7.20, CN7.22, CN10.9, CN10.20, CN10.32, J1.A1, J1.A12, J1.B1, J1.B12, J1.SH, J2.A1, J2.A12, J2.B1, J2.B12, J2.SH, J3.3, J3.5, J3.9, LD2.1, LD3.1, R1.2, R2.2, R3.2, R6.2, R9.2, R10.2, R12.2, R14.2, R15.2, R23.2, TP1.1, TP2.1, TP3.1, TP4.1, U1.12, U1.18, U1.31, U1.47, U1.63, U2.3, U2.12, U2.21, U3.2, U4.4, U5.1, U6.1, Y1.2, Y1.4

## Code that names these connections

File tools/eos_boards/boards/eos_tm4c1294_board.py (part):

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  dimension drawing, Figure 4-1 (p. 26). Used as mechanical and pinout facts only.

Form factor (SPMU365C Figure 4-1, read off the drawing in inches from the lower-left corner; here in
mm from the top-left): outline 4.9 x 2.2 in. BoosterPack 2's ten-pin rows run from x = 1.45 in (pin
10) to 2.35 in (pin 1), BoosterPack 1's from 3.95 to 4.85 in, each site with its outer rows 0.05 in
and 1.85 in from the top edge and its inner rows 0.15 in and 1.75 in (outer rows 1.8 in apart, inner
1.6 in, as the 40-pin standard has them); both sites face the same way, pin 1 at the right end of
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(inner, even pins), J2 its rows C (inner, odd) and D (outer, even); J3 and J4 the same for
BoosterPack 2; J5 is the 98-hole breakout, pin n = hole n.

  BP1 A: 3V3 PE4 PC4 PC5 PC6 PE5 PD3 PC7 PB2 PB3     B: 5V GND PE0 PE1 PE2 PE3 PD7 PA6 PM4 PM5
  BP1 C: PF1 PF2 PF3 PG0 PL4 PL5 PL0 PL1 PL2 PL3     D: GND PM3 PH2 PH3 RST PD1 PD0 PN2 PN3 PP2
  BP2 A: 3V3 PD2 PP0 PP1 PD4* PD5* PQ0 PP4 PN5 PN4   B: 5V GND PB4 PB5 PK0 PK1 PK2 PK3 PA4 PA5
  BP2 C: PG1 PK4 PK5 PM0 PM1 PM2 PH0 PH1 PK6 PK7     D: GND PM7 PP5 PA7 RST PQ2+PA3 PQ3+PA2 PP3 PQ1 PM6

  * BP2 A.5/A.6 carry PD4/PD5 (UART2) or, with JP1/JP2 turned, PA0/PA1 (CAN0Rx/CAN0Tx, Table 26-5
    encoding 7), the bridge then moving to UART2; PQ2/PA3 and PQ3/PA2 share BP2 D.6/D.7 through 0 ohm
    links R40/R41 (SPI MOSI/MISO and I2C8 SDA/SCL, as SPMU365C 2.1.6.2 describes), so firmware keeps
    the unused one of each an input. Breakout hole 58 has PB0 through 1 kohm (errata GPIO#09), hole
    60 (PB1) is not connected: PB1 senses USB VBUS here. Hole 34 is VREFA+ (see below).

Every value follows a data sheet:

* Supply: VDD, VDDA (pin 8) and VREFA+'s link on one 3.3 V rail, the inner layer 4 plane (the guide
  3.4.1, 3.4.4: VDD and VDDA "connected directly to the same +3.3V power source"; data sheet Table
  27-6, VDD 2.97-3.63 V). 0.1 uF X7R 0402 at the VDD pins, each joined to its pin before routing (the
  guide 3.4.3: "one decoupling capacitor in close proximity to each power-supply pin"; Figure 18): one
  each at pins 7, 16, 39, 47, 69, 79, 90, 101, 113 and 122, one shared by 26 and 28 (PQ3 between
  them) and one by 51 and 52 (adjacent). Those of pins 39, 51/52 and 90 (C4, C6, C46), and RST's
  10 nF (C27), sit on the bottom side under the chip, as the guide's 128-pin example (Table 7) puts
  most of its capacitors on the back: each pin reaches its capacitor through a via inside the pad
  ring, and the pins' outer ends stay free for their neighbours' escapes (on the top side they had
  boxed PG0/PG1, PA2/PA4 and PM4 in, and pin 90 had no way to the plane). Ground pins 17, 48, 80, 114
  and GNDA 10 are joined to their neighbour capacitor's ground pad, which has its via to the inner
  ground plane; pins 55 and 58 (between the Ethernet pins) go inward to C6's ground pad. 10 uF bulk near
  the chip (the guide 3.4.3: VDD and VDDA bulk "typically between 2 uF and 22 uF"). VDDA: 1 uF and
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  In the guide's order: pin 115 drops through a via inside the pad ring to the 2.2 uF (C19), nearest,
  then the 1 uF (C20) and the 0.1 uF (C21), all three on the bottom side under the chip beside that
  via, each ground pad with a via of its own to the ground plane; on the top side the pins round
  pin 115 leave no room for a 0603 at its end, and a capacitor there boxed PJ0 (pin 116) in. Pin 87
  drops through its own via to its 0.1 uF (C22, bottom side) and on, through the bottom layer, to C20
  (the device USB pair runs between the two pins inside the pad ring). VDDC feeds nothing else.
* ADC reference: VREFA+ (pin 9) from the 3.3 V rail through a 0 ohm link R43 with 1 uF + 0.01 uF to
  GNDA at the pin (the guide 3.4.5: VREFA+ to VDDA when the ADC need not be precise, CREF 1 uF and
  0.01 uF "as close as possible"; Table 26-7). It also reaches breakout hole 34: remove R43 to feed
  an external reference there (data sheet Table 27-34 note c: no current-limiting resistor).
* 25 MHz crystal (the integrated PHY needs 25 MHz +-50 ppm, data sheet Tables 27-50, 27-16 note; the
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  guide 4.15 suggests 1 Mohm, "connected to the same supply voltage that the VBAT pin is connected
  to": the data sheet's figure for a crystal is followed), the button to ground through 470 ohm at
  the pin (the guide 3.5.1 asks for a series resistor on a switch); also breakout hole 95.
* HIB (pin 65) and the Ethernet termination supply: "When entering hibernation in VDD3ON mode, the
  supply rails to the Ethernet resistors R1, R2, R3, R4 found in Figure 20-13 ... must be switched
  off" (data sheet 7.3.9 and the note under Figure 20-13). HIB is asserted (low) in hibernation
  whatever the VDD3ON bit says (HIBCTL, bit 8) and, with VDD3ON set, must not switch the 3.3 V
  regulator. So HIB drives the ON pin of a TI TPS22917 load switch (SLVSDW8B: active-high ON, VIH
  1 V, 80-110 mohm at 3.3-5 V) that makes ETH_VTERM, the supply of the four 49.9 ohm resistors.
  The transformer's centre taps are on ETH_VTERM too: their windings join them to the same lines
  in DC, so leaving them on 3.3 V would hold the lines at 3.3 V with the resistors' supply off
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* Ethernet (data sheet 20.4.3 and Figure 20-13; the guide 4.1): EN0TXOP/EN0TXON/EN0RXIP/EN0RXIN each
  pulled to ETH_VTERM, the switched 3.3 V (see HIB above), by 49.9 ohm 1 % at the chip, one
  terminal on the line (the guide 4.1.1, 3.3.8);
  RBIAS 4.87 kohm 1 % within 6 mm of pin 59 with its own ground via (the guide 4.1.4; data sheet
  Table 27-49: 4.82-4.92 kohm). Magnetics and jack: Wurth Elektronik 7499010121A (WE-RJ45LAN, data
  sheet version 003.001, 2024-07-26: 10/100BASE-TX, 1:1 +-2 % on transmit and receive with centre
  taps, 350 uH minimum, common-mode chokes, Bob Smith termination 4 x 75 ohm and 1000 pF 2 kV to pin
  8, shielded, tab up, green LED 10 (+) to 9, yellow LED 12 (+) to 11, VF 1.8-2.4 V at 20 mA). A
  symmetrical 1:1 transformer is what the data sheet asks for Auto-MDIX (20.4.3). Centre taps (2,
  5) on ETH_VTERM, each with its own 1 uF on the bottom side beside its pin (data sheet Figure 20-13
  note: "located near the physical pins of the transformer"; the guide 4.1.2). Shield and pin 8 are chassis, tied to ground through 1 Mohm and
  4.7 nF 2 kV (data sheet Figure 20-13). ESD: TI TPD4EUSB30 (SLVSAC2G: 5.5 V standoff, 0.8 pF DQA,
  IEC 61000-4-2 level 4), one per pair on the device side between the termination and the jack (the
  guide 4.1.6, which names this position for a device-side array), lines passing straight through
  its flow-through pads. The tab-up jack's pins run in the same order as the chip's (RD-, RD+, TD-,
  TD+ against EN0RXIN, EN0RXIP, EN0TXON, EN0TXOP), so the pairs reach it MDI-wired, with no crossing
  and no via. Jack LEDs on PF0 (EN0LED0) and PF4 (EN0LED1), sourcing current (the guide 4.1.7), 470
  ohm: (3.3 - 1.8) / 470 = 3.2 mA.
* Layout rules for the pairs (the guide 4.1.8, 3.2.3.2, 3.3.8): top layer over the inner ground
  plane, 100 ohm differential target, each pair's lines length-matched within 1.27 mm, the pairs 1.27 mm
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* USB device port (J7, USB-C): USB0DP/USB0DM (PL6/PL7) straight to the connector through an
  SP0503BAHTG (Littelfuse SP05xxBA: three TVS channels to ground, 5.5 V standoff, <= 100 nA); the PHY
  has its own D+ pull-up (data sheet 21.2 note). 5.1 kohm Rd on CC1 and CC2 (TI SLVSFJ9 10.3.14.2).
  VBUS to PB1 (USB0VBUS) through 100 ohm (the guide 4.3.1; PB1 is the one 5 V-tolerant pin, data
  sheet 27.14; the errata GPIO#09 workaround 2 points to these USB rules), so firmware can drop the
  pull-up when the host leaves (data sheet 21.2 note: a self-powered device must watch VBUS). A 10
  kohm bleed takes VBUS down within tens of ms of an unplug. Device only: firmware forces device mode
  (USBGPCS DEVMOD), so PB0 is a free GPIO.
* Debug: a 10-pin Cortex Debug header (the guide Table 9) on PC0-PC3 and RST in place of TI's
  on-board ICDI, whose firmware is TI's: Samtec FTSH-105-01-L-DV-K, keyed. The chip's JTAG pins
  have internal pull-ups, enough while the lines are under 2 in (the guide 3.7.1).
* USB-UART (J6): CP2102N-A02-GQFN20 (Silicon Labs CP2102N data sheet Rev. 1.5) as on EoS TM4C123
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  3.10). 4.7 uF + 0.1 uF on VREGIN and on VDD, 1 kohm RSTb pull-up (section 2.1). VBUS sense: the
  22.1 kohm / 47.5 kohm divider of Figure 2.6 (5 V reads 3.41 V, 4.4 V reads 3.0 V, above VIH = VIO -
  0.6 V, Table 3.7) plus a 5.1 kohm bleed: the pin stays under VIL = 0.6 V unless over 185 uA is pushed
  into VDBG, and only the TPS2116's leakage into its unselected input can push any. TXD and RXD reach UART0 (PA0/PA1,
  the guide 4.6's debug UART and the ROM boot loader's) through 1 kohm each, which caps a driver fight
  at 3.3 mA, and through jumpers JP1/JP2 (see above). ESD: SP0503BAHTG (CP2102N Figure 2.5).
* Power: each USB-C port has a Littelfuse 1206L075THYR polyfuse (1206L data sheet, revised 10/29/21:
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  drop 0.16 V, and the 0.3 mm 5 V tracks (most of them on inner layers) add the drop the README's
  Layout section measures. Power LED: Kingbright APTD1608LCGCK (DSAO7432, VF 1.9 V typ at 2 mA) through
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
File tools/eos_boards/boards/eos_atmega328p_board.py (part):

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  CBUS = 100 nF), 500 mA polyfuse (Littelfuse 1206L series datasheet: 1206L050 holds 0.50 A,
  trips at 1.00 A, 6 V, R 0.150 ohm min, R1max 0.700 ohm). A USBLC6-style part, with diodes
  from D+/D- to its VBUS pin, is safe here because the CH340C senses no VBUS: it has no VBUS
  pin (CH340 V3D section 4) and is itself powered from VUSB, so its D+ pull-up dies with the
  host's VBUS and cannot hold VBUS up after an unplug. U1 sits turned so that each line runs
  in on one pin and out of the opposite one (D- 4 -> 3, D+ 6 -> 1), ST's flow-through layout
  (DS4260 section 2.3, Figure 6).
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

# Shield headers, by pin 1, and the ICSP header (positions: see the module docstring).
D0_PIN = uno(2500, 2000)      # D0 .. D7 run right to left, 100 mil apart
D8_PIN = uno(1640, 2000)      # D8 .. D13, GND, AREF, SDA, SCL run right to left
POWER_PIN = uno(1100, 100)    # NC, IOREF, RESET, 3V3, 5V, GND, GND, VIN run left to right
A0_PIN = uno(2000, 100)       # A0 .. A5 run left to right
ICSP_PIN = uno(2505, 1200)    # pin 1 (MISO); pins 1-3-5 run down, 2-4-6 one column to the right
HOLES = [uno(600, 2000), uno(550, 100), uno(2600, 1400), uno(2600, 300)]

PARTS = [
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    # ---- ATmega328P -------------------------------------------------------------------------------------
    Part("U6", "MCU_Microchip_ATmega:ATmega328P-A", "ATmega328P-AU", "Package_QFP:TQFP-32_7x7mm_P0.8mm", (300, 260),
         {"VCC": "+5V", "GND": "GND", "AVCC": "AVCC", "AREF": "AREF", "ADC6": NC, "ADC7": NC,
          "XTAL1/PB6": "XTAL1", "XTAL2/PB7": "XTAL2", "~{RESET}/PC6": "RESET",
          "PD0": "D0", "PD1": "D1", "PD2": "D2", "PD3": "D3", "PD4": "D4", "PD5": "D5", "PD6": "D6", "PD7": "D7",
          "PB0": "D8", "PB1": "D9", "PB2": "D10", "PB3": "D11", "PB4": "D12", "PB5": "D13",
          "PC0": "A0", "PC1": "A1", "PC2": "A2", "PC3": "A3", "PC4": "A4_SDA", "PC5": "A5_SCL"},
         fields={"Manufacturer": "Microchip", "MPN": "ATMEGA328P-AU",
                 "Description": f"8-bit AVR, 32 KB flash, 16 MHz at 5 V, TQFP-32 ({MCU_DS})"}),
    cap("C12", "100n", "+5V", "GND", (350, 205), f"Capacitor 100 nF 50 V X7R 0603 (VCC pin 6 / GND pin 5, {AN2519} 2.1)"),
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# Board placement: (x, y, rotation) in mm, origin top-left. USB-C and the barrel jack on the left
# edge, roughly where the Uno R3 drawings show its USB and power jacks; shield headers, ICSP and
# holes exactly where the drawings put them. The MCU sits under the digital headers, turned so its
# PB4..PD5 side faces D12..D5; crystal and decoupling on its right, AVCC filter on its left, reset
# parts below it. Power on the lower left, the L LED and its buffer on the lower right; a corridor
# is kept clear right of the power parts for A0..A5.
PLACEMENT = {
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    rules={"min_track": 0.127},
    netclasses={"Power": {"track": 0.4, "clearance": 0.15}, "Supply": {"track": 0.3, "clearance": 0.15},
                "USB": {"track": 0.2, "clearance": 0.15}},
    # AVCC in the 0.3 mm class: it also powers PC0-PC3's drivers (DS40002061B 1.1.7)
    net_to_class={"VBUS": "Power", "VJACK": "Power", "VIN": "Power", "BUCK_SW": "Power",
                  "5V_REG": "Supply", "VUSB": "Supply", "+5V": "Supply", "+3V3": "Supply", "AVCC": "Supply",
                  "USB_D+": "USB", "USB_D-": "USB"},
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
